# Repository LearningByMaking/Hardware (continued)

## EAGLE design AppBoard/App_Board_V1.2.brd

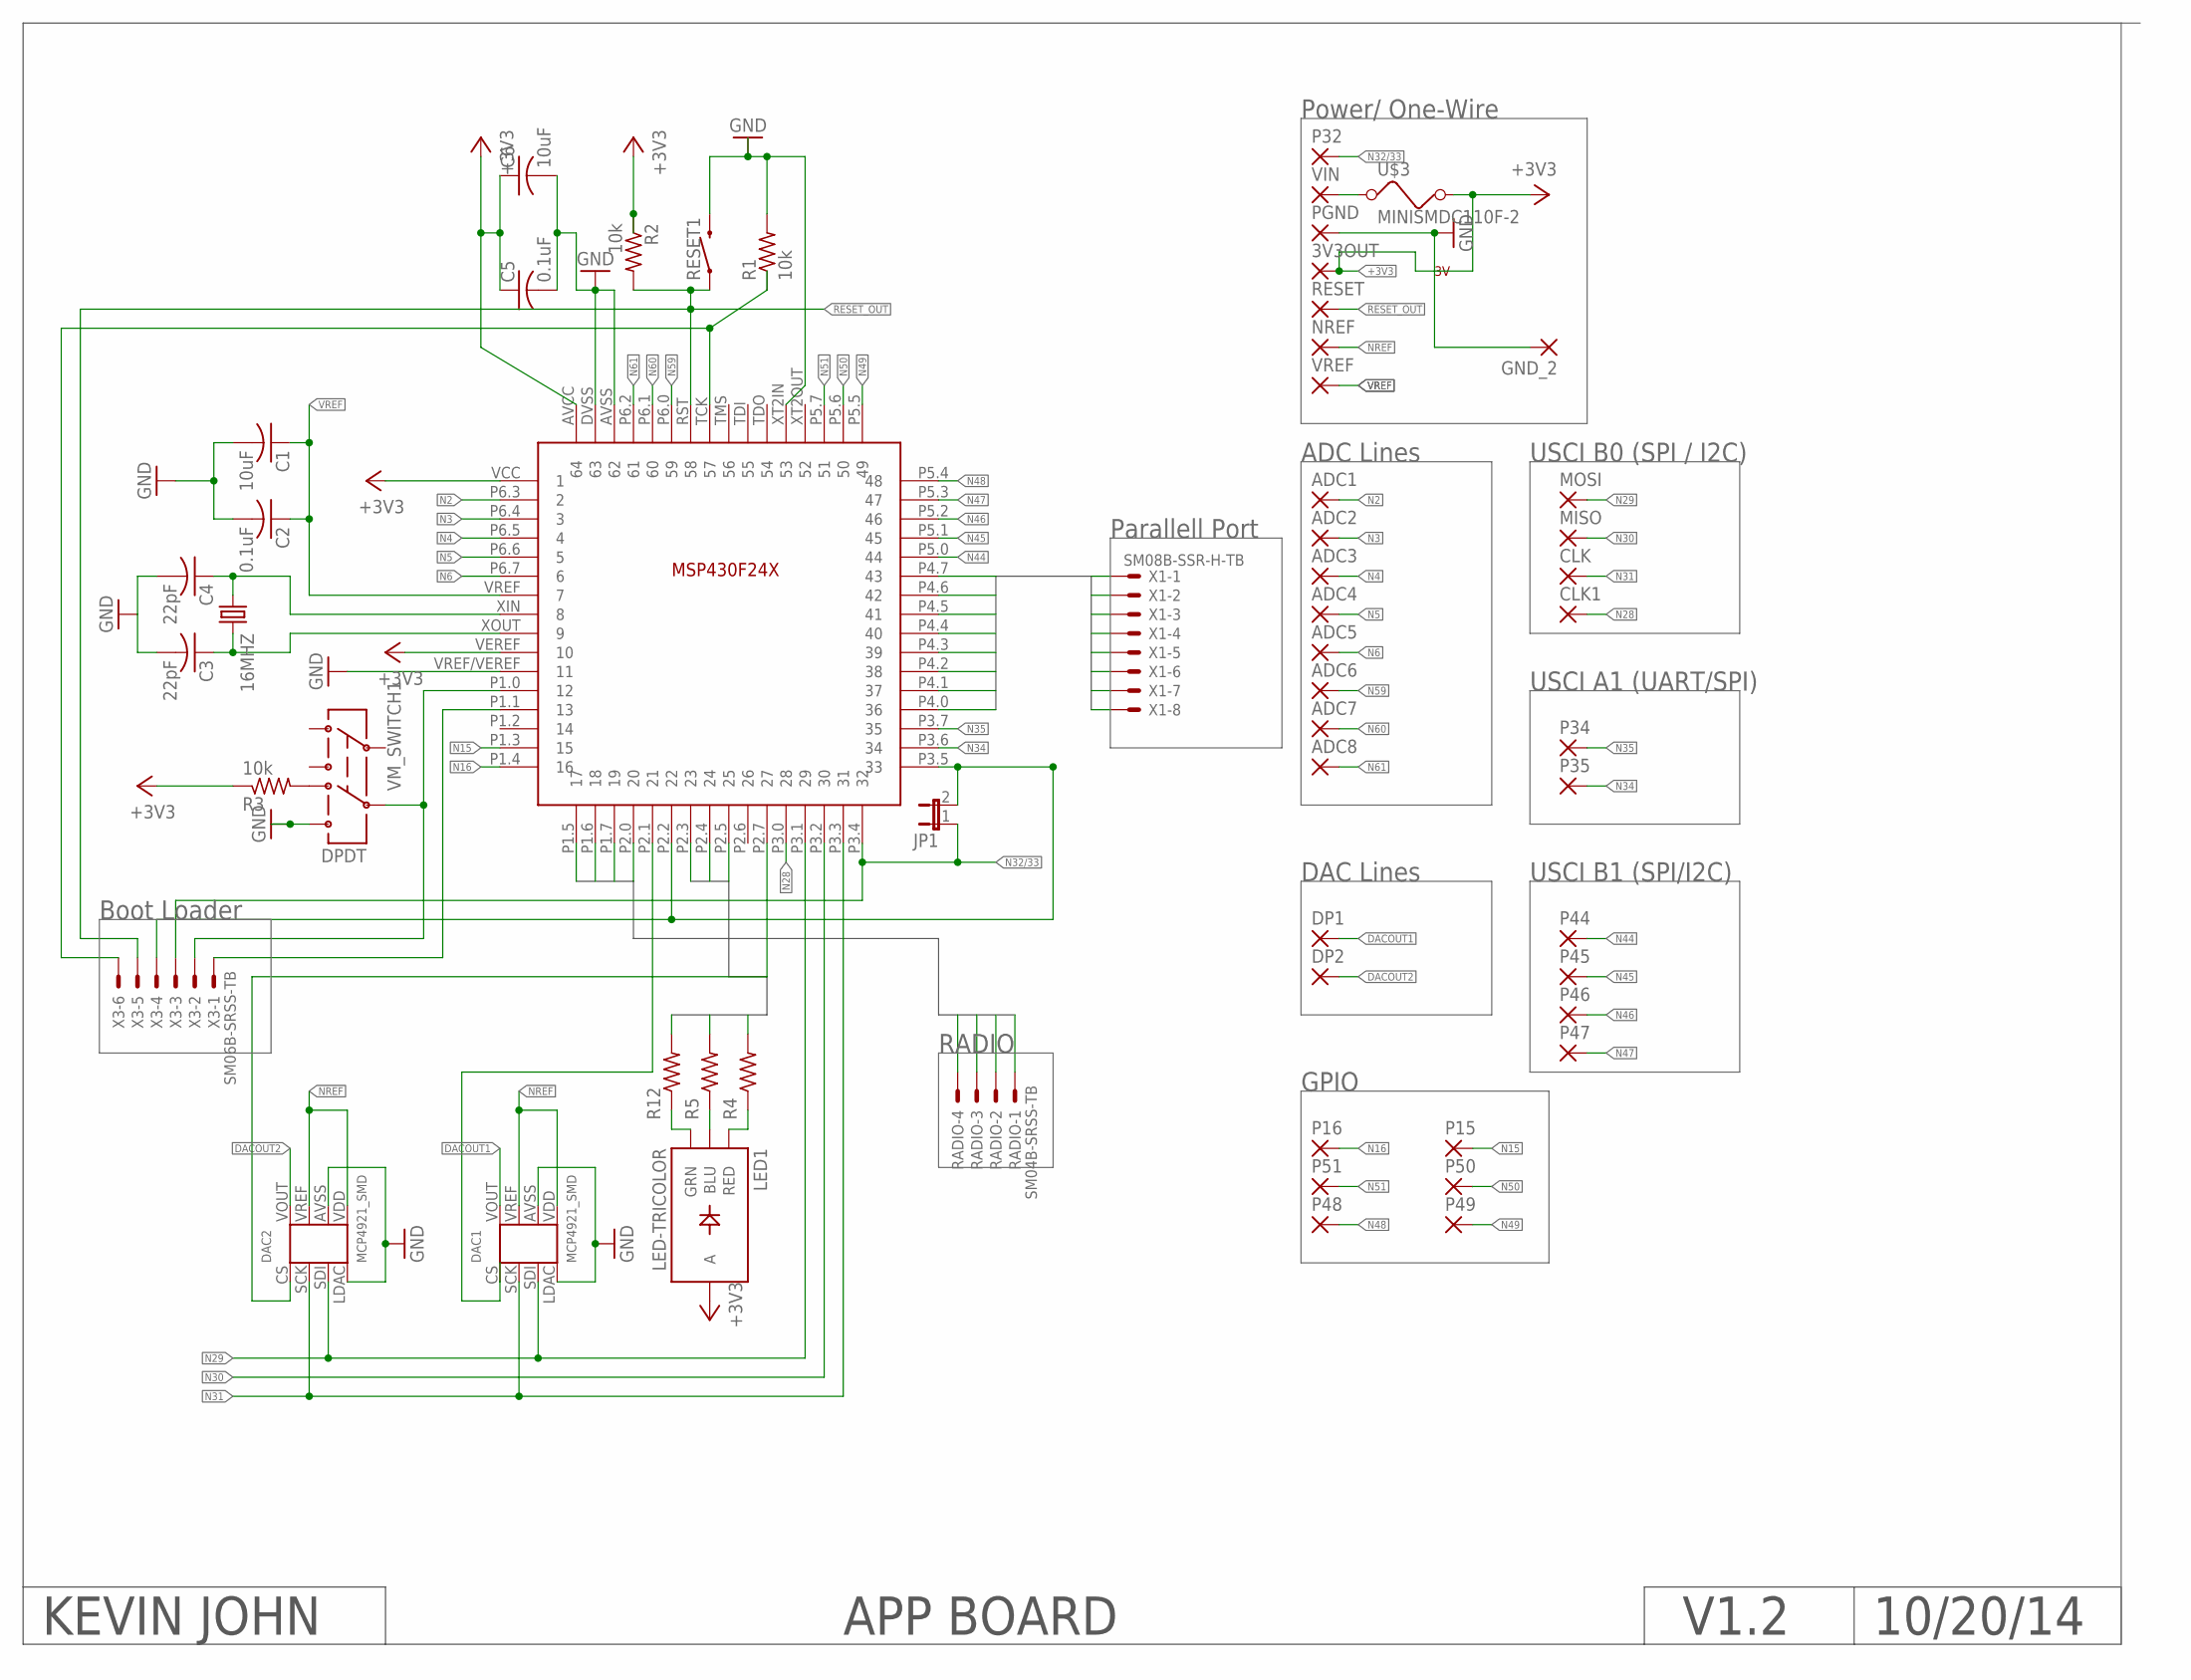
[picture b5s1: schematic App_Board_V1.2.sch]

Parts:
3V3OUT: 1,6/0,9
16MHZ: CRYSTAL5X3; CRYSTAL-SMD-5X3
ADC1, ADC2, ADC3, ADC4, ADC5, ADC6, ADC7, ADC8: 1,6/0,9
C1: 10uF; C0805
C2, C5: 0.1uF; C0805
C3, C4: 22pF; C0805
C6: 10uF; C1210
CLK, CLK1: 1,6/0,9
DAC1, DAC2: MCP4921_SMD
DP1, DP2: 1,6/0,9
GND_2: 1,6/0,9
JP1: JP1E; JP1
LED1: LED-TRICOLOR; LED-TRICOLOR-SMD
MISO: 1,6/0,9
MOSI: 1,6/0,9
NREF: 1,6/0,9
P15, P16, P32, P34, P35, P44, P45, P46, P47, P48, P49, P50, P51: 1,6/0,9
PGND: 1,6/0,9
R1, R2, R3: 10k; R0603
R4, R5, R12: 100; R0603
RADIO: SM04B-SRSS-TB
RESET: 1,6/0,9
RESET1: SWITCH-MOMENTARY-2SMD; TACTILE_SWITCH_SMD
U$1: MSP430
U$3: MINISMDC110F-2; MINISMDC110
VIN: 1,6/0,9
VM_SWITCH1: DPDT; AYZ0202
VREF: 1,6/0,9
X1: SM08B-SSR-H-TB
X3: SM06B-SRSS-TB

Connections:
3.3VOUT: U$3.P$1 (1), VIN.1
+3V3: 3V3OUT.1, C5.1, C6.1, LED1.A, R2.1, R3.1, U$1.AVCC (64), U$1.VCC (1), U$1.VEREF (10), U$3.P$2 (2)
DACOUT1: DAC1.VOUT, DP1.1
DACOUT2: DAC2.VOUT, DP2.1
GND: C1.2, C2.2, C3.2, C4.2, C5.2, C6.2, DAC1.AVSS (VCC), DAC1.LDAC (LADC), DAC2.AVSS (VCC), DAC2.LDAC (LADC), GND_2.1, PGND.1, R1.2, RESET1.3 (2), U$1.AVSS (62), U$1.DVSS (63), U$1.VREF/VEREF (11), U$1.XT2IN (53), VM_SWITCH1.6
LED0: R5.2, U$1.P2.3 (23)
LED1: R12.2, U$1.P2.4 (24)
LED2: R4.2, U$1.P2.5 (25)
N2: ADC1.1, U$1.P6.3 (2)
N3: ADC2.1, U$1.P6.4 (3)
N4: ADC3.1, U$1.P6.5 (4)
N5: ADC4.1, U$1.P6.6 (5)
N6: ADC5.1, U$1.P6.7 (6)
N15: P15.1, U$1.P1.3 (15)
N16: P16.1, U$1.P1.4 (16)
N20: DAC2.CS, U$1.P2.7 (27)
N28: CLK1.1, U$1.P3.0 (28)
N29: DAC1.SDI, DAC2.SDI, MOSI.1, U$1.P3.1 (29)
N30: MISO.1, U$1.P3.2 (30)
N31: CLK.1, DAC1.SCK, DAC2.SCK, U$1.P3.3 (31)
N32: JP1.2, U$1.P2.2 (22), U$1.P3.5 (33), X3.4
N32/33: JP1.1, P32.1, U$1.P3.4 (32), X3.3
N34: P35.1, U$1.P3.6 (34)
N35: P34.1, U$1.P3.7 (35)
N44: P44.1, U$1.P5.0 (44)
N45: P45.1, U$1.P5.1 (45)
N46: P46.1, U$1.P5.2 (46)
N47: P47.1, U$1.P5.3 (47)
N48: P48.1, U$1.P5.4 (48)
N49: P49.1, U$1.P5.5 (49)
N50: P50.1, U$1.P5.6 (50)
N51: P51.1, U$1.P5.7 (51)
N59: ADC6.1, U$1.P6.0 (59)
N60: ADC7.1, U$1.P6.1 (60)
N61: ADC8.1, U$1.P6.2 (61)
unnamed: 16MHZ.1, C4.1, U$1.XIN (8)
unnamed: R3.2, VM_SWITCH1.4
unnamed: LED1.G (GRN), R12.1
unnamed: LED1.B (BLU), R5.1
unnamed: LED1.R (RED), R4.1
unnamed: U$1.P1.0 (12), VM_SWITCH1.5, X3.2
unnamed: DAC1.CS, U$1.P2.1 (21)
unnamed: 16MHZ.3 (2), C3.1, U$1.XOUT (9)
unnamed: U$1.P1.1 (13), X3.1
NREF: DAC1.VDD, DAC1.VREF, DAC2.VDD, DAC2.VREF, NREF.1
RADIO_IRQ: RADIO.3, U$1.P1.6 (18)
RADIO_RX: RADIO.2, U$1.P1.7 (19)
RADIO_SELECT: RADIO.4, U$1.P1.5 (17)
RADIO_TX: RADIO.1, U$1.P2.0 (20)
RESET_OUT: R2.2, RESET.1, RESET1.1, U$1.RST (58), X3.5
RTS1: R1.1, U$1.TCK (57), X3.6
SERIAL0: U$1.P4.7 (43), X1.1
SERIAL1: U$1.P4.6 (42), X1.2
SERIAL2: U$1.P4.5 (41), X1.3
SERIAL3: U$1.P4.4 (40), X1.4
SERIAL4: U$1.P4.3 (39), X1.5
SERIAL5: U$1.P4.2 (38), X1.6
SERIAL6: U$1.P4.1 (37), X1.7
SERIAL7: U$1.P4.0 (36), X1.8
VREF: C1.1, C2.1, U$1.VREF (7), VREF.1

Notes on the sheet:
KEVIN JOHN
APP BOARD
V1.2
10/20/14
Power/ One-Wire
ADC Lines
DAC Lines
Parallell Port
USCI B0 (SPI / I2C)
Boot Loader
USCI A1 (UART/SPI)
USCI B1 (SPI/I2C)
GPIO
RADIO

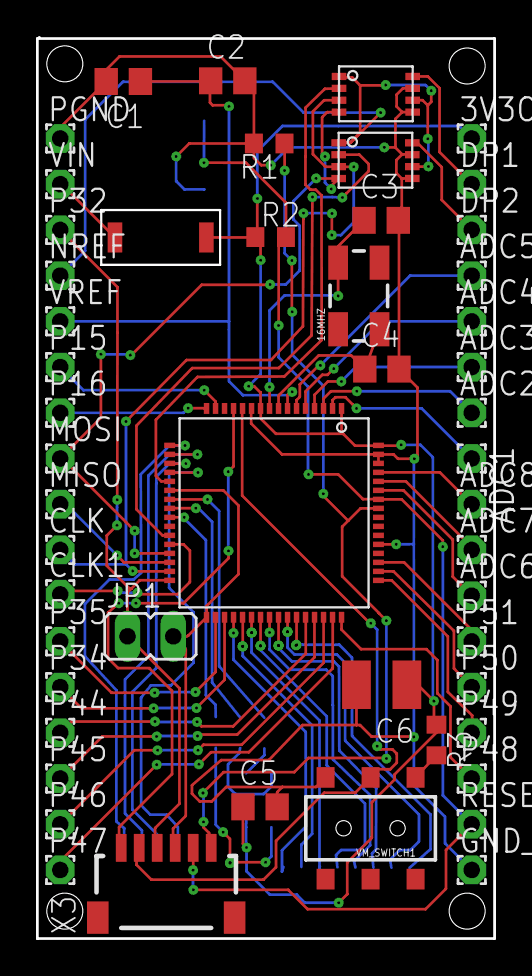
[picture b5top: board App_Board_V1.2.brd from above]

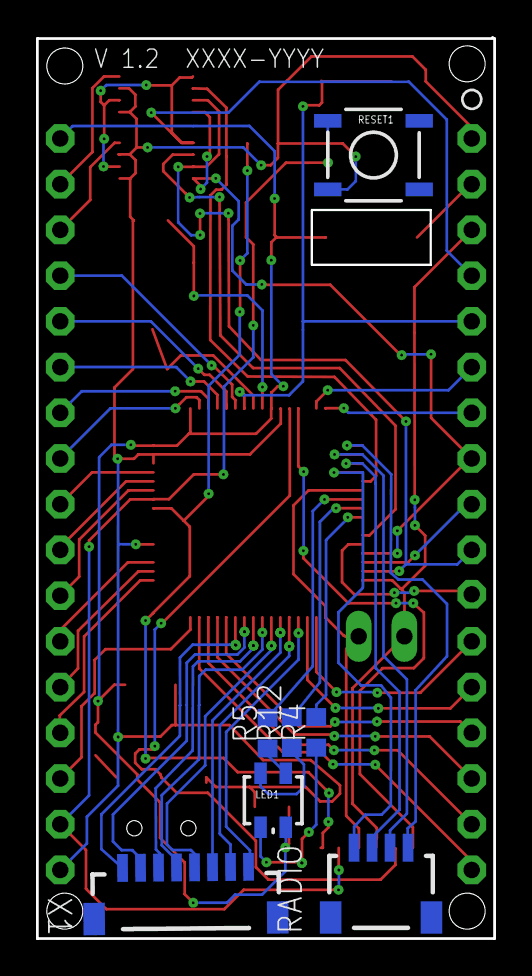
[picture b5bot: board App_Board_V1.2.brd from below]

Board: 2 copper layers, 25.4 x 50.0 mm, 58 parts (7 on the bottom side), 60 nets.

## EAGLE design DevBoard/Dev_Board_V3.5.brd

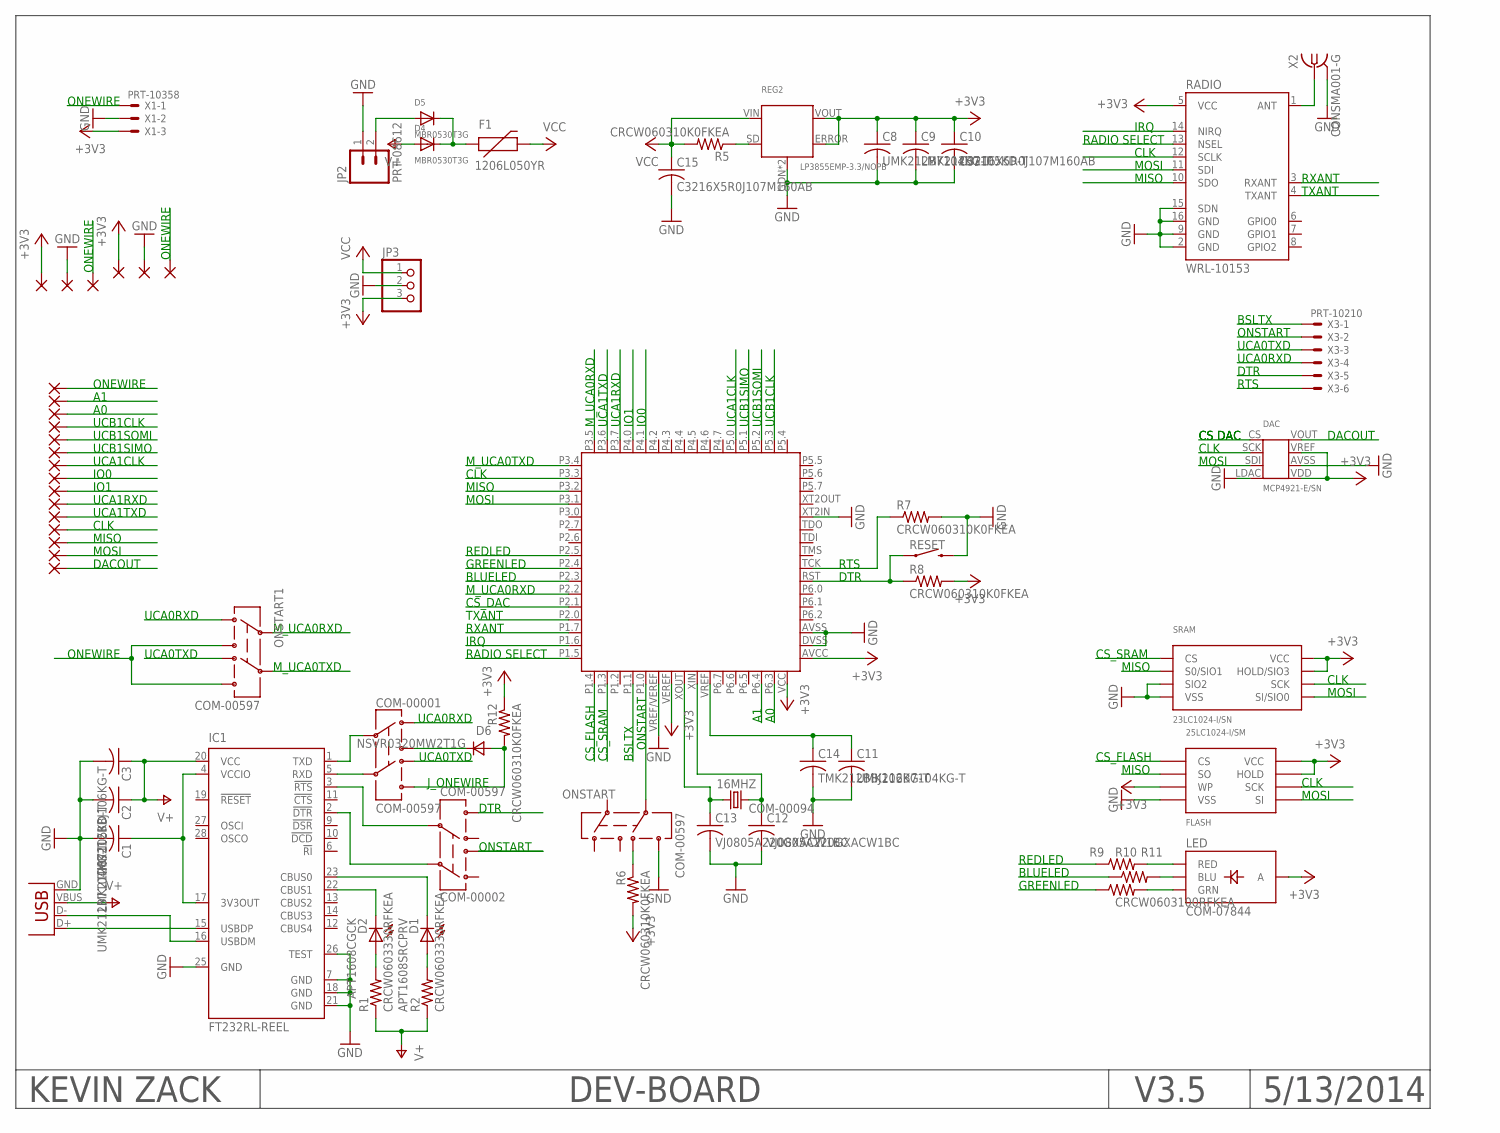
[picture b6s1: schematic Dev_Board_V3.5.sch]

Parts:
16MHZ: COM-00094; CRYSTAL-SMD-5X3
+3.1, +3.3: 1,6/0,9
A0, A1, A2, A3, A4: 1,6/0,9
C1, C8, C11: UMK212B7104KG-T; C0805
C2, C9: LMK212B7105KD-T; C0805
C3, C14: TMK212BBJ106KG-T; C0805
C10, C15: C3216X5R0J107M160AB; C1206
C12, C13: VJ0805A220GXACW1BC; C0805
CLK: 1,6/0,9
COM-00001, COM-00002: COM-00597; AYZ0202
D1: APT1608SRCPRV; LED-0603
D2: APT1608CGCK; LED-0603
D4, D5: MBR0530T3G; SOD-123
D6: NSVR0320MW2T1G; SOD323; MPN CDSOD323-T05C
DAC: MCP4921-E/SN; MCP4921_SMD
DACOUT: 1,6/0,9
F1: 1206L050YR; PTC-1206
FLASH: 25LC1024-I/SM; 25LC1024
GND, GND26: 1,6/0,9
IC1: FT232RL-REEL; SSOP28
IO0, IO1: 1,6/0,9
JP1: 1734035-2; USB-MINIB-NOSTOP
JP2: PRT-08612; JST-2-SMD
JP3: PINHD-1X3; 1X03
LED: COM-07844; LED-TRICOLOR-SMD
MISO: 1,6/0,9
MOSI: 1,6/0,9
ONSTART, ONSTART1: COM-00597; AYZ0202
R1, R2: CRCW0603330RFKEA; R0603
R5, R6, R7, R8, R12: CRCW060310K0FKEA; R0603
R9, R10, R11: CRCW0603100RFKEA; R0603
RADIO: WRL-10153; RFM22-XXX-S2
REG2: LP3855EMP-3.3/NOPB; LP3855EMP
RESET: COM-08720; TACTILE_SWITCH_SMD
SRAM: 23LC1024-I/SN; 23LC1024
U$3: MSP430F2410TPMR; MSP430F248
UCA1CLK, UCA1RXD, UCA1TXD: 1,6/0,9
UCB1CLK, UCB1SIMO, UCB1SOMI: 1,6/0,9
X1: PRT-10358; BM03B-SRSS-TB
X2: CONSMA001-G; BU-SMA-V
X3: PRT-10210; SM06B-SRSS-TB

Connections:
+3V3: +3.1.1, +3.3.1, C8.1, C9.1, C10.1, DAC.VDD, DAC.VREF, FLASH.HOLD, FLASH.VCC, FLASH.WP, JP3.3, LED.A, R6.2, R8.2, R12.1, RADIO.5 (VCC), REG2.ERROR, REG2.VOUT, SRAM.HOLD/SIO3, SRAM.VCC, U$3.AVCC, U$3.VCC (DVCC), U$3.VEREF, X1.3
A0: A0.1, U$3.P6.3
A1: A1.1, U$3.P6.4
BLUELED: R10.1, U$3.P2.3
BSLTX: U$3.P1.1, X3.1
CLK: CLK.1, DAC.SCK, FLASH.SCK, RADIO.12 (SCLK), SRAM.SCK, U$3.P3.3
CSRADIO: RADIO.13 (NSEL), U$3.P1.5
CS_DAC: DAC.CS, U$3.P2.1
CS_FLASH: FLASH.CS, U$3.P1.4
CS_SRAM: SRAM.CS, U$3.P1.3
DACOUT: DAC.VOUT, DACOUT.1
DTR: COM-00002.6, R8.1, RESET.1, U$3.RST, X3.5
GND: C1.2, C2.2, C3.2, C8.2, C9.2, C10.2, C11.2, C12.2, C13.2, C14.2, C15.2, DAC.AVSS (VCC), DAC.LDAC (LADC), FLASH.VSS, GND.1, GND26.1, IC1.7 (GND), IC1.18 (GND), IC1.21 (GND), IC1.25 (GND), IC1.26 (TEST), JP1.GND, JP2.1 (2), JP3.2, ONSTART.6, R7.2, RADIO.2 (GND), RADIO.9 (GND), RADIO.15 (SDN), RADIO.16 (GND), REG2.GDN (GND), REG2.GND, RESET.3 (2), SRAM.SIO2, SRAM.VSS, U$3.AVSS, U$3.DVSS, U$3.VREF/VEREF, U$3.XT2IN, X1.2, X2.2 (GND), X2.3 (GND), X2.4 (GND), X2.5 (GND)
GREENLED: R11.1, U$3.P2.4
IO0: IO0.1, U$3.P4.1
IO1: IO1.1, U$3.P4.0
IRQ: RADIO.14 (NIRQ), U$3.P1.6
MISO: FLASH.SO, MISO.1, RADIO.10 (SDO), SRAM.SO/SIO1 (S0/SIO1), U$3.P3.2
MOSI: DAC.SDI, FLASH.SI, MOSI.1, RADIO.11 (SDI), SRAM.SI/SIO0, U$3.P3.1
M_UCA0RXD: ONSTART1.2, U$3.P2.2, U$3.P3.5
M_UCA0TXD: ONSTART1.5, U$3.P3.4
unnamed: D1.C, IC1.23 (CBUS0)
unnamed: IC1.16 (USBDM), JP1.D-
unnamed: IC1.15 (USBDP), JP1.D+
unnamed: C1.1, IC1.4 (VCCIO), IC1.17 (3V3OUT)
unnamed: D2.C, IC1.22 (CBUS1)
unnamed: D2.A, R1.2
unnamed: D1.A, R2.2
unnamed: R5.1, REG2.SD
unnamed: D5.A, JP2.2 (1)
unnamed: COM-00001.5, IC1.5 (RXD)
unnamed: ONSTART.4, R6.1
unnamed: LED.R (RED), R9.2
unnamed: RADIO.1 (ANT), X2.1
unnamed: LED.B (BLU), R10.2
unnamed: C11.1, C14.1, U$3.VREF
unnamed: LED.G (GRN), R11.2
unnamed: COM-00001.3, D6.1 (C)
unnamed: D4.C, D5.C, F1.1
unnamed: COM-00002.5, IC1.3 (!RTS)
unnamed: 16MHZ.1, C13.1, U$3.XOUT
unnamed: 16MHZ.3 (2), C12.1, U$3.XIN
unnamed: COM-00001.2, IC1.1 (TXD)
unnamed: COM-00001.6, D6.2 (A), R12.2
unnamed: COM-00002.2, IC1.2 (!DTR)
ONEWIRE: A2.1, A3.1, A4.1, ONSTART1.3, ONSTART1.6, X1.1
ONSTART: COM-00002.3, ONSTART.5, U$3.P1.0, X3.2
REDLED: R9.1, U$3.P2.5
RTS: R7.1, U$3.TCK, X3.6
RXANT: RADIO.3 (RXANT), U$3.P1.7
TXANT: RADIO.4 (TXANT), U$3.P2.0
UCA0RXD: COM-00001.1, ONSTART1.1, X3.4
UCA0TXD: COM-00001.4, ONSTART1.4, X3.3
UCA1CLK: U$3.P5.0, UCA1CLK.1
UCA1RXD: U$3.P3.7, UCA1RXD.1
UCA1TXD: U$3.P3.6, UCA1TXD.1
UCB1CLK: U$3.P5.3, UCB1CLK.1
UCB1SIMO: U$3.P5.1, UCB1SIMO.1
UCB1SOMI: U$3.P5.2, UCB1SOMI.1
V+: C2.1, C3.1, D4.A, IC1.20 (VCC), JP1.VBUS, R1.1, R2.1
VCC: C15.1, F1.2, JP3.1, R5.2, REG2.VIN

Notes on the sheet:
CS DAC
CLK
MOSI
DACOUT
MISO
ONSTART
BSLTX
CS_SRAM
CS_FLASH
RADIO SELECT
IRQ
RXANT
TXANT
REDLED
BLUELED
GREENLED
UCB1SOMI
UCB1SIMO
UCA1CLK
UCB1CLK
UCA1TXD
UCA1RXD
IO1
IO0
KEVIN ZACK
DEV-BOARD
V3.5
5/13/2014
UCA0RXD
UCA0TXD
DTR
RTS
ONEWIRE
M_UCA0RXD
M_UCA0TXD
J_ONEWIRE
CS_DAC

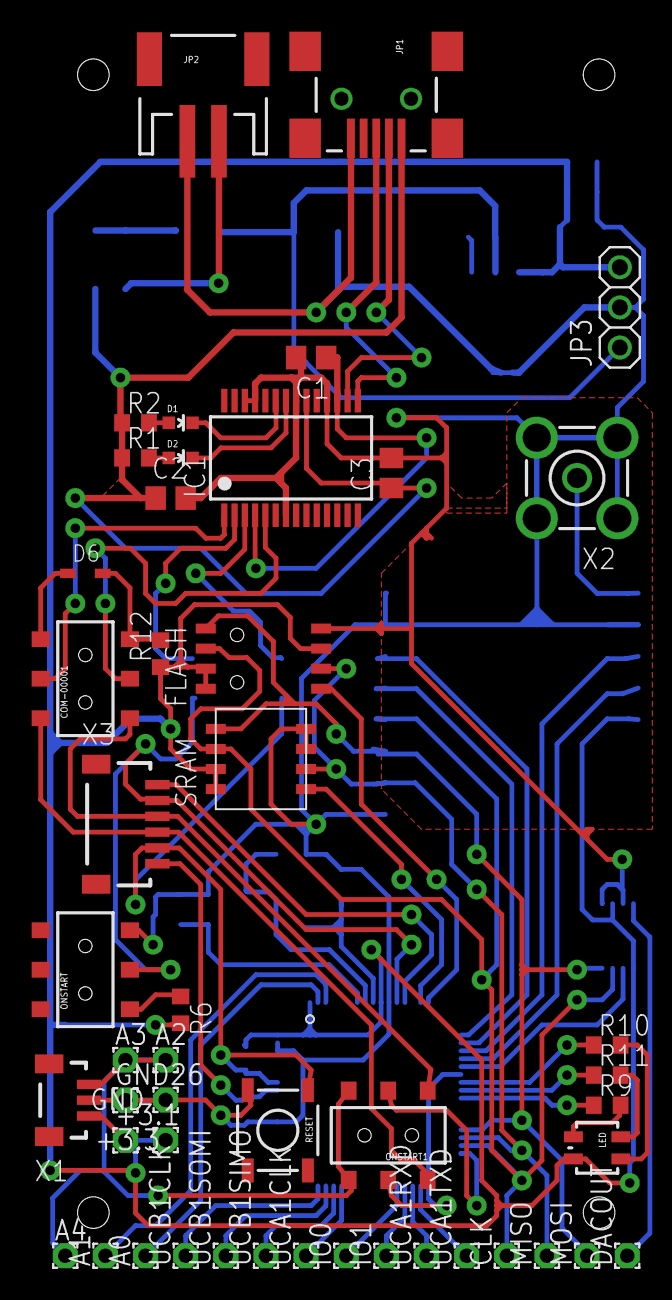
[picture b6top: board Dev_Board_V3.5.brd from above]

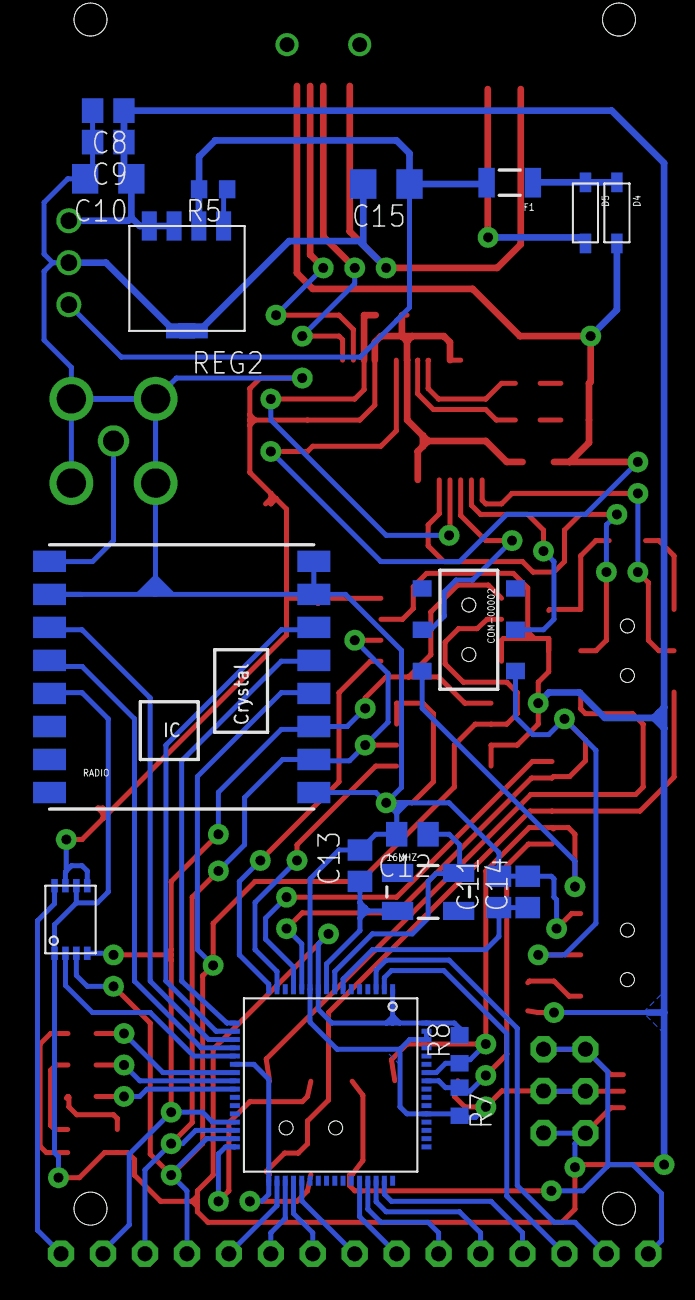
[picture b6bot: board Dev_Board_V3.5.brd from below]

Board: 2 copper layers, 68 parts (20 on the bottom side), 61 nets.

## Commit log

2015-01-09 Added all the existing files I have to initialize the repo
2015-02-04 Dimension adjustments of the "Appcore_Reveiver" package
    Adjustments to the dimensions of the package diagram "Appcore_Reveiver"
    were made to match the dimension of the "App_Board_V1.2" eagle diagram's
    pins and holes placements.
2015-02-13 Mirrored the App_Core library template
    The package template for the App Board v1.2 was flipped horizontally to
    match the foot print orientation it has when used to creating breakout
    boards.
2016-04-11 created new uStar layout
2016-04-11 added changes submitted by Ben
2016-04-20 added power management circuits and SD card
2016-04-20 added ADC lines instead of the uneeded ground
2016-05-10 fixed clearance violations
2016-05-13 refined and executed the DRC process, made appropriate changes
2016-06-02 added order files and protoboard files
2016-06-02 added gerber files for ustar and protoboard
2016-07-07 updates and stuff
